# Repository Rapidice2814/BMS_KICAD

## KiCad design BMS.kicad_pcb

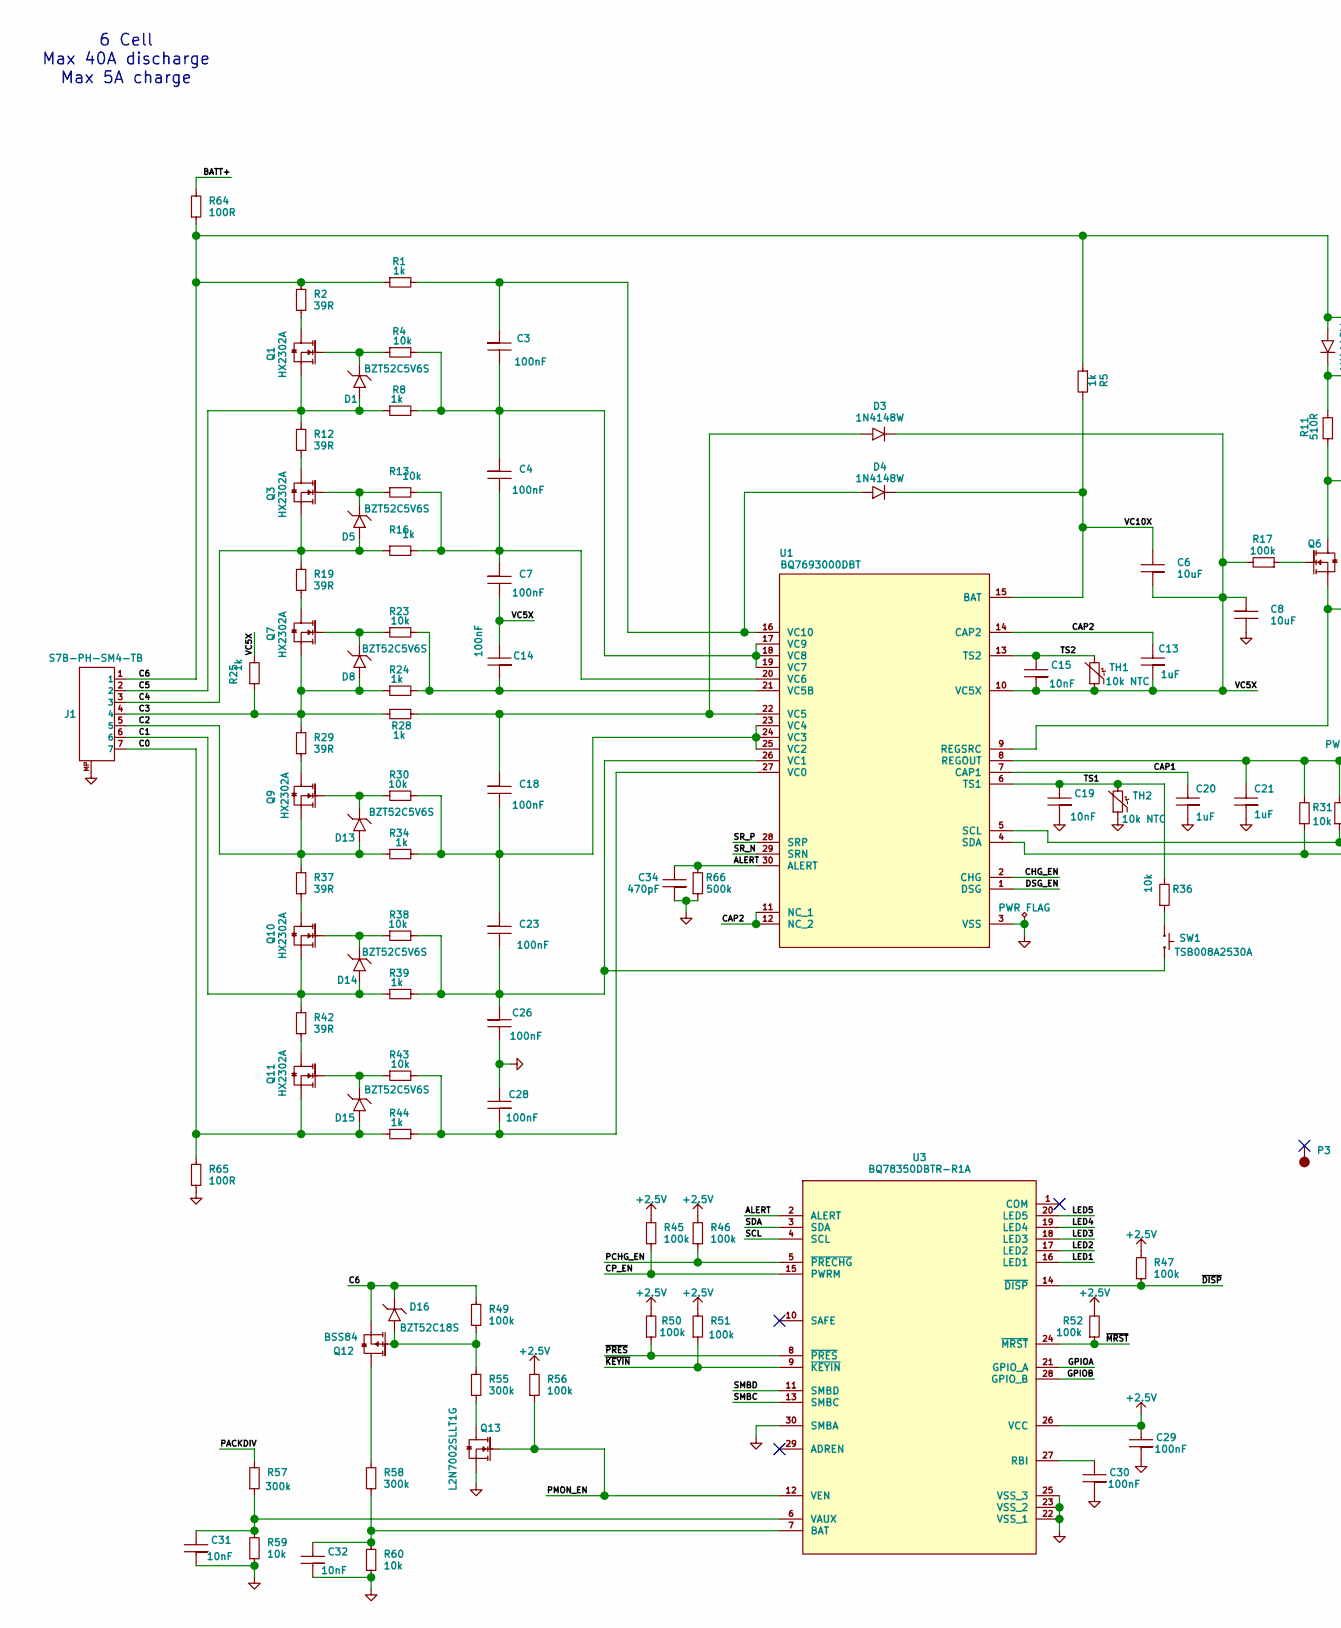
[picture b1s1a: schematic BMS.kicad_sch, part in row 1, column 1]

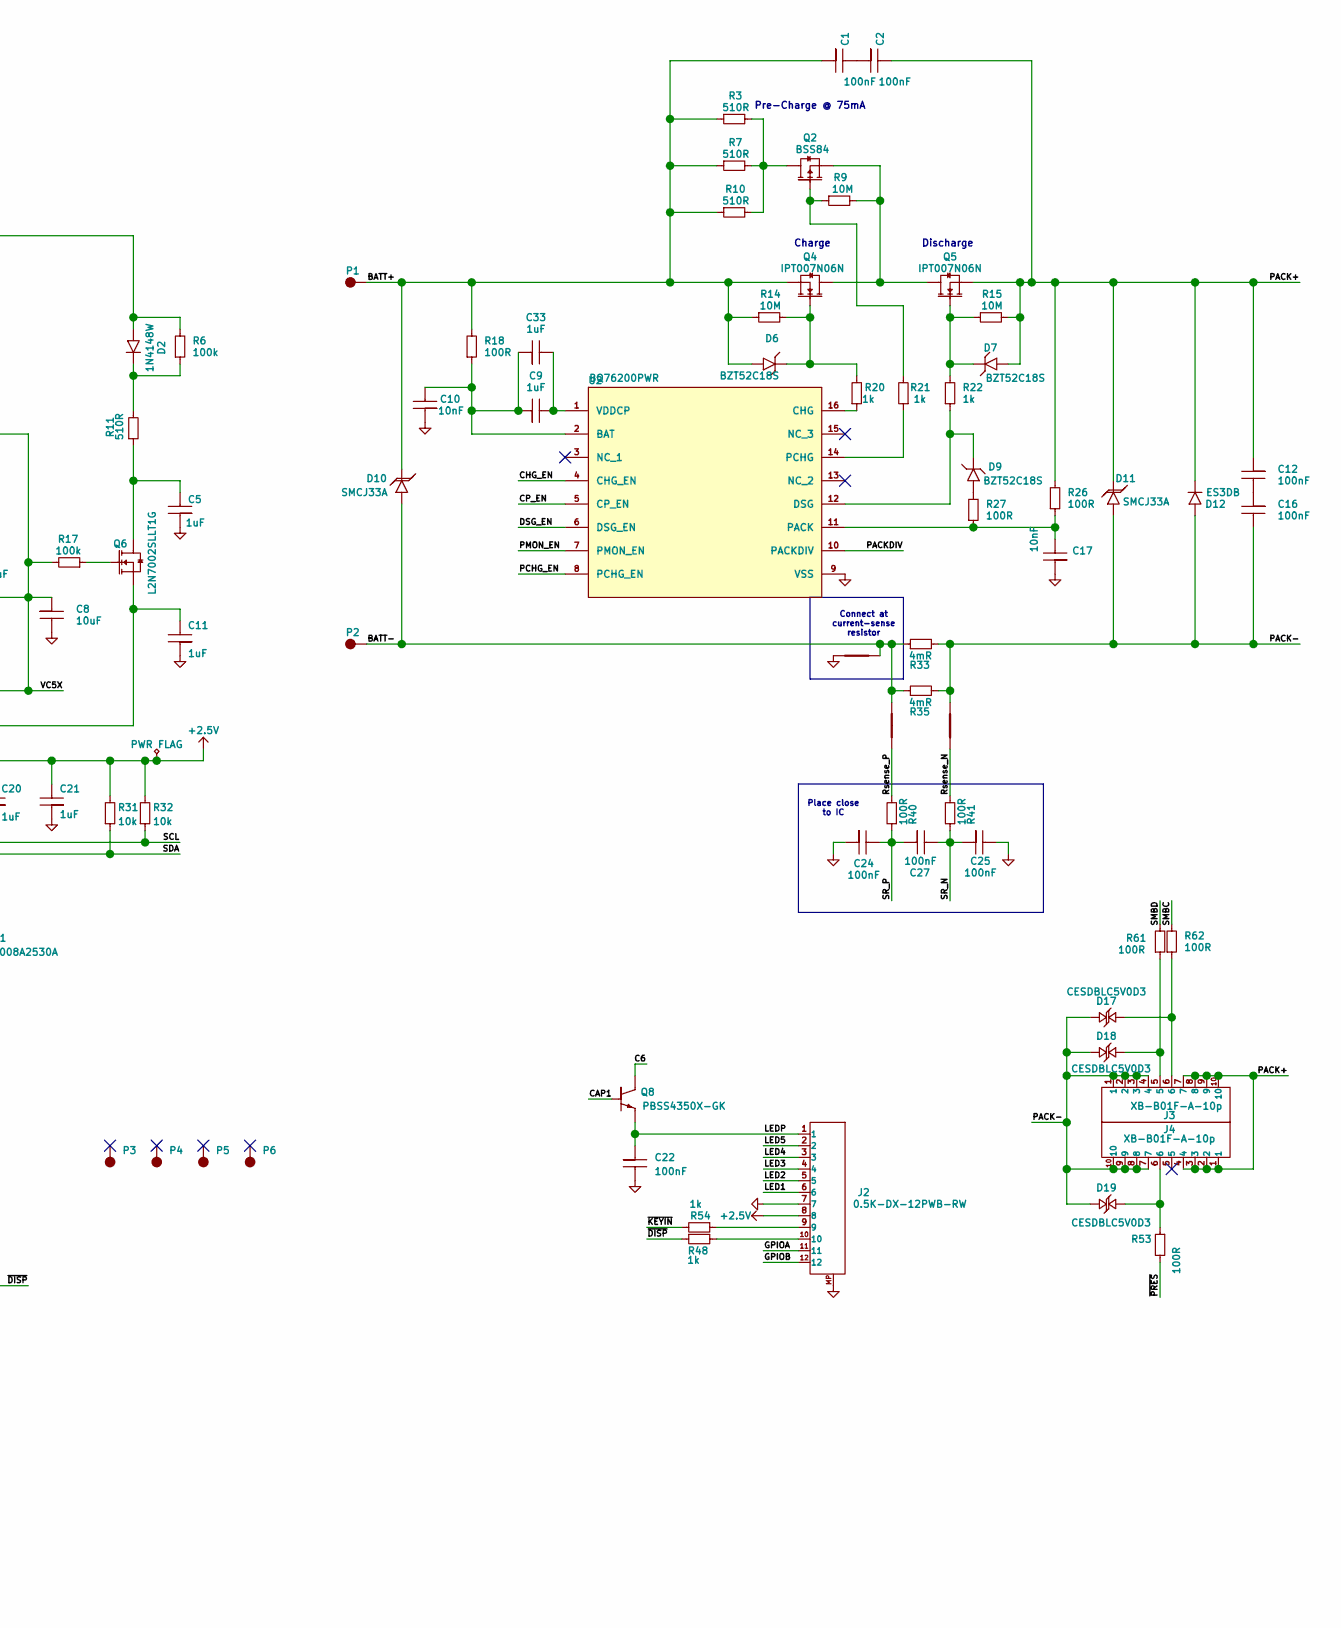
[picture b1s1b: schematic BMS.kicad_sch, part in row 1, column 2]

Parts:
C1, C2, C3, C4, C7, C12, C14, C16, C18, C22, C23, C24, C25, C26, C27, C28, C29, C30: 100nF; C0603; Voltage Rating Voltage?; PartsBox ID a3f0c242x8g9f90p8xydqhvt4c
C5, C9, C11, C13, C20, C21, C33: 1uF; C0603; Voltage Rating Voltage?; PartsBox ID 13v5km39a6hgt88xq1v23rfjkr
C6, C8: 10uF; C1206; Voltage Rating Voltage?; PartsBox ID eh4mz6v3ftjj79s52wt7j3cj7n
C10, C15, C17, C19, C31, C32: 10nF; C0603; Voltage Rating Voltage?; PartsBox ID 8mrd1tqpa2g3898zxsnjzqp0qw
C34: 470pF; C0603; Voltage Rating Voltage?; PartsBox ID 0sd417sz5jg8y9ebegymrv2cq2
D1, D5, D8, D13, D14, D15: BZT52C5V6S; SOD323; Zener Voltage 5.6V; Power Rating 200mW; MPN BZT52C5V6S
D2: 1N4148W; SOD123; Voltage Rating 100V; Current Rating 130mA; MPN 1N4148W
D3, D4: 1N4148W; SOD123; Voltage Rating 100V; Current Rating 150mA; MPN 1N4148W
D6, D7: BZT52C18S; SOD323; Zener Voltage 16V; MPN BZT52C18S
D9, D16: BZT52C18S; SOD323; Zener Voltage 18V; MPN BZT52C18S
D10, D11: SMCJ33A; SMC(DO-214AB); Power Rating Power?; MPN SMCJ33A GFM-TD
D12: ES3DB; SMB(DO-214AA); Voltage Rating 200V; Current Rating 100A; MPN ES3DB
D17, D18, D19: CESDBLC5V0D3; SOD323; Power Rating Power?; MPN CESDBLC5V0D3
J1: S7B-PH-SM4-TB; MPN HCZZ0451-7
J2: 0.5K-DX-12PWB-RW; FFC_0.5mm_12p; MPN 0.5K-DX-12PWB-RW
J3, J4: XB-B01F-A-10p; MPN XB-B01F-A-10p
NT1: NetTie_2; NetTie-2_SMD_Pad1.0mm
NT2, NT3: NetTie_2; NetTie-2_SMD_Pad0.2mm
P1, P2: SMDPad_10x10mm
P3, P4, P5, P6: THTPad_M2_Screw
Q1, Q3, Q7, Q9, Q10, Q11: HX2302A; NMOS_SOT23-3; MPN HX2302A
Q2, Q12: BSS84; PMOS_SOT23-3; MPN BSS84
Q4, Q5: IPT007N06N; NMOS_HSOF-8; MPN IPT007N06N
Q6, Q13: L2N7002SLLT1G; NMOS_SOT23-3; MPN L2N7002SLLT1G
Q8: PBSS4350X-GK; NPN_SOT_89-3; MPN PBSS4350X-GK
R1, R5, R8, R16, R20, R21, R22, R24, R25, R28, R34, R39, R44, R48, R54: 1k; R0603; PartsBox ID 7s1b3fkf0yg1c9c3wf27b6vtf0
R2, R12, R19, R29, R37, R42: 39R; R1206; PartsBox ID bbkrxmr5mwkfn8srxbjpnbrzk7
R3, R7, R10, R11: 510R; R1206; Power Rating 500mW; PartsBox ID 9htgakrpvek86abdvbx5hd0k18
R4, R13, R23, R30, R31, R32, R36, R38, R43, R59, R60: 10k; R0603; PartsBox ID 8g7rj3n0e8k1yb0y1admgn1v6f
R6, R17, R45, R46, R47, R49, R50, R51, R52, R56: 100k; R0603; PartsBox ID 0yvf6a224ej1n90nm1kzw2cmp3
R9, R14, R15: 10M; R0603; PartsBox ID cxmp64nge8jqh9fgfezcbr2fgb
R18, R26, R27, R40, R41, R53, R61, R62, R64, R65: 100R; R0603; PartsBox ID 3bkajqnqpgk7m9nmjzxqwkfmfb
R33, R35: 4mR; R2512; Power Rating 5W; MPN YHR2512WE5WR004F3
R55, R57, R58: 300k; R0603; PartsBox ID 348pvetbn2hep8vkj3xhp38k0j
R66: 500k; R0603; PartsBox ID 6c7pn866spjp5b12t2sxb7arfv
SW1: TSB008A2530A; Button_6x3.5mm_2P_SMD; MPN TSB008A2530A
TH1: 10k NTC; NTC_THT; MPN MF52A103F3950 (A1)
TH2: 10k NTC; NTC_0603; MPN KNTC0603/10KF3950
U1: BQ7693000DBT; TSSOP-30; Manufacturer_Part_Number BQ7693000DBT
U2: BQ76200PWR; TSSOP-16; Manufacturer_Part_Number BQ76200PWR
U3: BQ78350DBTR-R1A; TSSOP-30; Manufacturer_Part_Number BQ78350DBT-R1A

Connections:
+2.5V: C21.2, C29.2, J2.8, R31.2, R32.2, R45.2, R46.2, R47.2, R50.2, R51.2, R52.2, R56.2, U1.8 (REGOUT), U3.26 (VCC)
/ALERT: C34.2, R66.2, U1.30 (ALERT), U3.2 (ALERT)
/BATT+: C1.1, D6.2 (A), D10.1 (C), P1.1 (Pad), Q4.S, R3.1, R7.1, R10.1, R14.1, R18.2, R64.2
/BATT-: D10.2 (A), NT1.2, NT2.1, P2.1 (Pad), R33.1, R35.1
/C0: D15.2 (A), J1.7, Q11.S, R44.1, R65.2
/C1: D14.2 (A), J1.6, Q10.S, R39.1, R42.2
/C2: D13.2 (A), J1.5, Q9.S, R34.1, R37.2
/C3: D8.2 (A), J1.4, Q7.S, R24.1, R25.1, R28.1, R29.2
/C4: D5.2 (A), J1.3, Q3.S, R16.1, R19.2
/C5: D1.2 (A), J1.2, Q1.S, R8.1, R12.2
/C6: D2.2 (A), D16.1 (C), J1.1, Q8.C, Q12.S, R1.1, R2.2, R5.1, R6.2, R49.2, R64.1
/CAP1: C20.2, Q8.B, U1.7 (CAP1)
/CAP2: C13.2, U1.11 (NC_1), U1.12 (NC_2), U1.14 (CAP2)
/CHG_EN: U1.2 (CHG), U2.4 (CHG_EN)
/CP_EN: R45.1, U2.5 (CP_EN), U3.15 (PWRM)
/DSG_EN: U1.1 (DSG), U2.6 (DSG_EN)
/GPIOA: J2.11, U3.21 (GPIO_A)
/GPIOB: J2.12, U3.28 (GPIO_B)
/LED1: J2.6, U3.16 (LED1)
/LED2: J2.5, U3.17 (LED2)
/LED3: J2.4, U3.18 (LED3)
/LED4: J2.3, U3.19 (LED4)
/LED5: J2.2, U3.20 (LED5)
/LEDP: C22.1, J2.1, Q8.E
/PACK+: C2.2, C12.1, D7.2 (A), D11.1 (C), D12.1 (C), J3.7, J3.8, J3.9, J3.10, J4.1, J4.2, J4.3, J4.4, Q5.S, R15.2, R26.2
/PACK-: C16.2, D11.2 (A), D12.2 (A), D17.1 (C), D18.1 (C), D19.1 (C), J3.1, J3.2, J3.3, J3.4, J4.7, J4.8, J4.9, J4.10, NT3.1, R33.2, R35.2
/PACKDIV: R57.2, U2.10 (PACKDIV)
/PCHG_EN: R46.1, U2.8 (PCHG_EN), U3.5 (~PRECHG)
/PMON_EN: Q13.G, R56.1, U2.7 (PMON_EN), U3.12 (VEN)
/Rsense_N: NT3.2, R41.2
/Rsense_P: NT2.2, R40.2
/SCL: R32.1, U1.5 (SCL), U3.4 (SCL)
/SDA: R31.1, U1.4 (SDA), U3.3 (SDA)
/SMBC: R62.2, U3.13 (SMBC)
/SMBD: R61.2, U3.11 (SMBD)
/SR_N: C25.1, C27.2, R41.1, U1.29 (SRN)
/SR_P: C24.2, C27.1, R40.1, U1.28 (SRP)
/TS1: C19.2, R36.2, TH2.2, U1.6 (TS1)
/TS2: C15.2, TH1.2, U1.13 (TS2)
/VC5X: C6.1, C7.2, C8.1, C13.1, C14.2, C15.1, D3.1 (C), R17.2, R25.2, TH1.1, U1.10 (VC5X)
/VC10X: C6.2, D4.1 (C), R5.2, U1.15 (BAT)
/~DISP: R47.1, R48.1, U3.14 (~DISP)
/~KEYIN: R51.1, R54.2, U3.9 (~KEYIN)
/~MRST: R52.1, U3.24 (~MRST)
/~PRES: R50.1, R53.2, U3.8 (~PRES)
GND: C5.1, C8.2, C10.1, C11.1, C17.1, C19.1, C20.1, C21.1, C22.2, C24.1, C25.2, C26.2, C28.2, C29.1, C30.1, C31.1, C32.1, C34.1, J1.MP, J2.7, J2.MP, NT1.1, Q13.S, R59.1, R60.1, R65.1, R66.1, TH2.1, U1.3 (VSS), U2.9 (VSS), U3.22 (VSS_1), U3.23 (VSS_2), U3.25 (VSS_3), U3.30 (SMBA)
unnamed: C1.2, C2.1
unnamed: C5.2, Q6.D, R11.1
unnamed: C12.2, C16.1
unnamed: D1.1 (C), Q1.G, R4.1
unnamed: D2.1 (C), R6.1, R11.2
unnamed: C18.1, D3.2 (A), R28.2, U1.22 (VC5)
unnamed: C3.1, D4.2 (A), R1.2, U1.16 (VC10)
unnamed: D5.1 (C), Q3.G, R13.1
unnamed: D6.1 (C), Q4.G, R14.2, R20.2
unnamed: D7.1 (C), Q5.G, R15.1, R22.2
unnamed: D8.1 (C), Q7.G, R23.1
unnamed: D9.2 (A), R27.2
unnamed: D9.1 (C), R22.1, U2.12 (DSG)
unnamed: D13.1 (C), Q9.G, R30.1
unnamed: D14.1 (C), Q10.G, R38.1
unnamed: D15.1 (C), Q11.G, R43.1
unnamed: D16.2 (A), Q12.G, R49.1, R55.2
unnamed: D17.2 (A), J3.6, R62.1
unnamed: D18.2 (A), J3.5, R61.1
unnamed: D19.2 (A), J4.6, R53.1
unnamed: J2.9, R54.1
unnamed: J2.10, R48.2
unnamed: Q1.D, R2.1
unnamed: Q2.D, R3.2, R7.2, R10.2
unnamed: Q2.G, R9.1, R21.2
unnamed: Q2.S, Q4.D, Q5.D, R9.2
unnamed: Q3.D, R12.1
unnamed: Q6.G, R17.1
unnamed: Q7.D, R19.1
unnamed: Q9.D, R29.1
unnamed: Q10.D, R37.1
unnamed: Q11.D, R42.1
unnamed: Q12.D, R58.2
unnamed: Q13.D, R55.1
unnamed: R36.1, SW1.1
unnamed: C11.2, Q6.S, U1.9 (REGSRC)
unnamed: C28.1, R43.2, R44.2, U1.27 (VC0)
unnamed: C23.2, C26.1, R38.2, R39.2, SW1.2, U1.26 (VC1)
unnamed: C18.2, C23.1, R30.2, R34.2, U1.23 (VC4), U1.24 (VC3), U1.25 (VC2)
unnamed: C14.1, R23.2, R24.2, U1.21 (VC5B)
unnamed: C4.2, C7.1, R13.2, R16.2, U1.20 (VC6)
unnamed: C3.2, C4.1, R4.2, R8.2, U1.17 (VC9), U1.18 (VC8), U1.19 (VC7)
unnamed: C9.1, C10.2, C33.1, R18.1, U2.2 (BAT)
unnamed: R20.1, U2.16 (CHG)
unnamed: C17.2, R26.1, R27.1, U2.11 (PACK)
unnamed: R21.1, U2.14 (PCHG)
unnamed: C9.2, C33.2, U2.1 (VDDCP)
unnamed: C32.2, R58.1, R60.2, U3.7 (BAT)
unnamed: C30.2, U3.27 (RBI)
unnamed: C31.2, R57.1, R59.2, U3.6 (VAUX)

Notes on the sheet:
Charge
Connect at current-sense resistor
Place close to IC
6 Cell Max 40A discharge Max 5A charge
Pre-Charge @ 75mA
Discharge

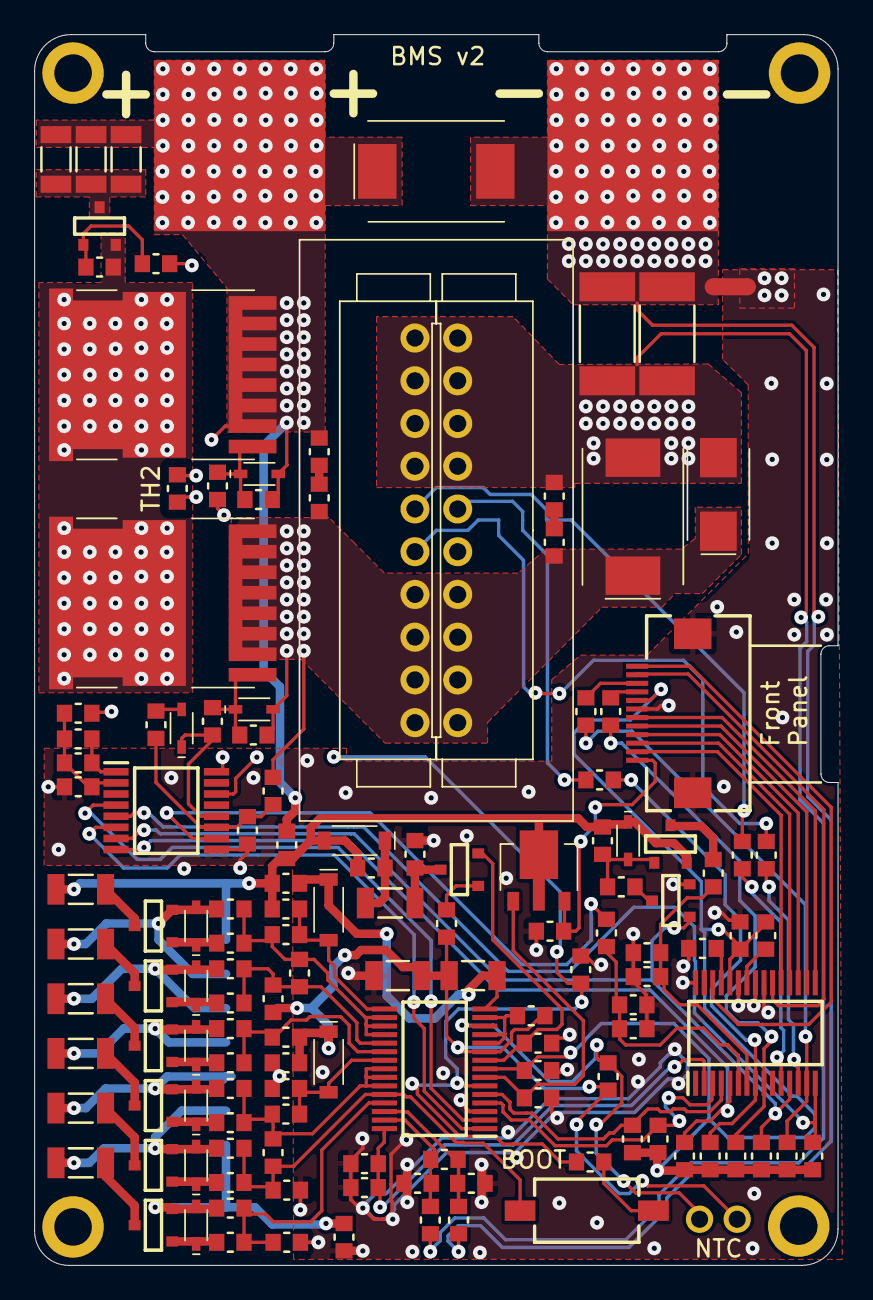
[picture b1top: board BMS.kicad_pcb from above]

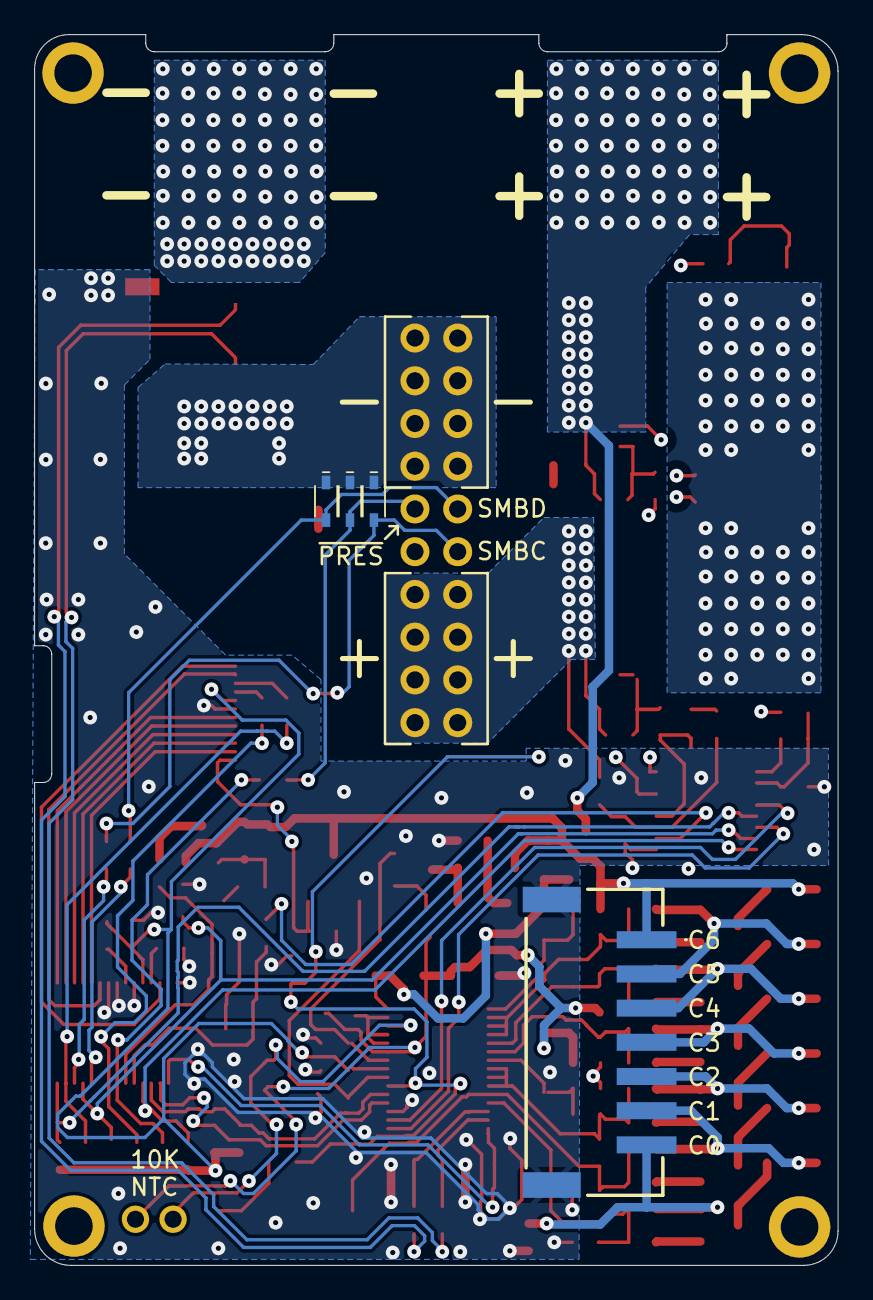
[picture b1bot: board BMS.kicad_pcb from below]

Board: 4 copper layers, 47.0 x 72.0 mm, 150 parts (4 on the bottom side), 96 nets.

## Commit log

2026-04-21 finished routing
2026-04-30 finished v2
